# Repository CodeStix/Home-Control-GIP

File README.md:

# Geïntegreerde proef: Home Control

Dit is een repo over mijn eindwerk voor de richting 6 elektriciteit-elektronica. Hier bevinden zich alle scripts, presentaties, schema's, documentaties ...

In het kort: een draadloos home-control systeem waarbij je eenvoudig en snel huishoudelijke apparaten kan aansturen via een gebruiksvriendelijke smartphone app zonder jezelf vragen te stellen over privacy.

Zie documentatie voor uitgebreide informatie.

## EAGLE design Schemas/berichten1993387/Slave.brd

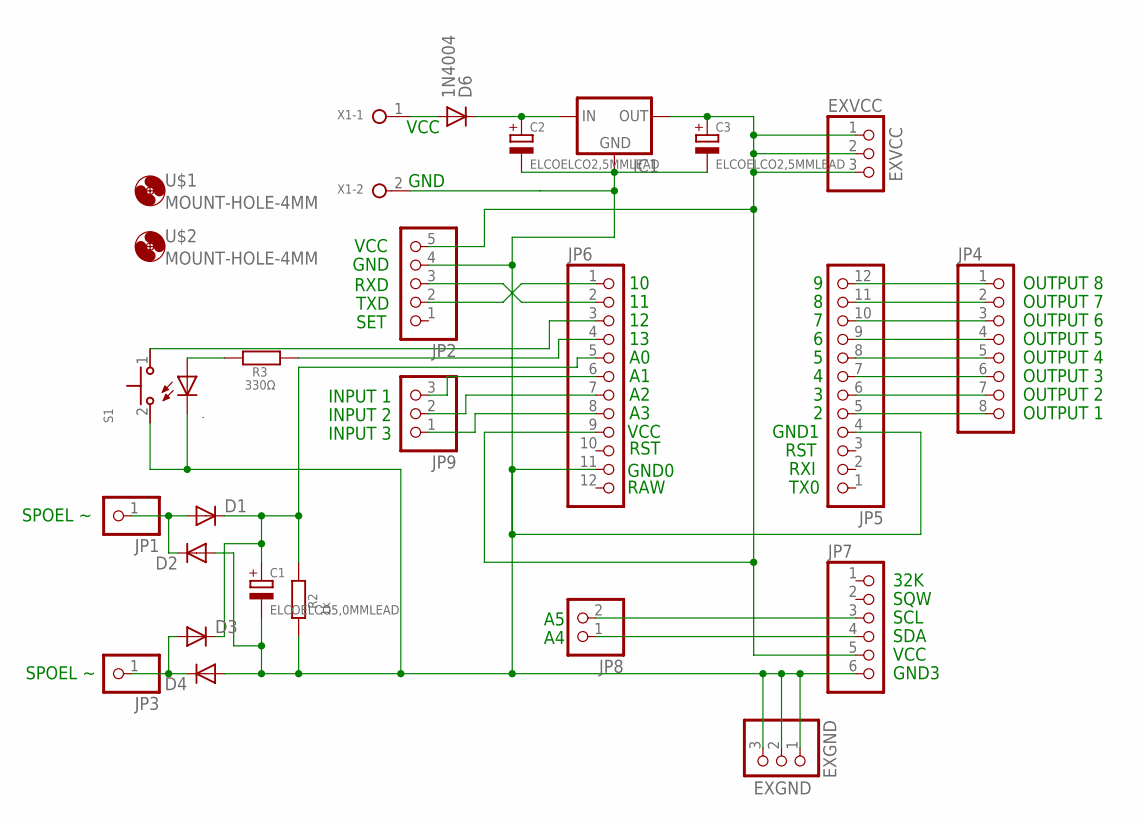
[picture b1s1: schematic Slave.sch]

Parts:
.: LED; CHIPLED_1206
C1: ELCOELCO5,0MMLEAD; ELCO5,0MMLEAD
C2, C3: ELCOELCO2,5MMLEAD; ELCO-2.5MMLEAD
D1, D2, D3, D4, D6: 1N4004; DO41-10
EXGND: PINHD-1X3; 1X03
EXVCC: PINHD-1X3; 1X03
IC1: 78XXS
JP1, JP3: PINHD-1X1; 1X01
JP2: PINHD-1X5; 1X05
JP4: PINHD-1X8; 1X08
JP5, JP6: PINHD-1X12; 1X12
JP7: PINHD-1X6; 1X06
JP8: PINHD-1X2; 1X02
JP9: PINHD-1X3; 1X03
R2: 1k; R1206W
R3: 330Ω; R1206W
S1: MICROSWITCH-B3U-1000P
U$1, U$2: MOUNT-HOLE-4MM; 4,0
X1: TERMINAL-5MM-2POLE; W237-132

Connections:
GND: ..C, C1.-, C2.-, C3.-, D2.A, D4.A, EXGND.1, EXGND.2, EXGND.3, IC1.GND, JP2.4, JP5.4, JP6.11, JP7.6, R2.1, S1.2, X1.2
unnamed: JP7.4, JP8.1
unnamed: JP7.3, JP8.2
unnamed: JP4.1, JP5.12
unnamed: JP4.2, JP5.11
unnamed: JP4.3, JP5.10
unnamed: JP4.4, JP5.9
unnamed: JP4.5, JP5.8
unnamed: JP4.6, JP5.7
unnamed: JP4.7, JP5.6
unnamed: JP4.8, JP5.5
unnamed: D1.A, D2.C, JP1.1
unnamed: C1.+, D1.C, D3.C, JP6.5, R2.2
unnamed: JP6.8, JP9.1
unnamed: D3.A, D4.C, JP3.1
unnamed: JP6.7, JP9.2
unnamed: JP6.6, JP9.3
unnamed: JP2.2, JP6.1
unnamed: JP6.4, R3.2
unnamed: JP2.3, JP6.2
unnamed: ..A, R3.1
unnamed: JP6.3, S1.1
VCC0: D6.A, X1.1
VCC1: C2.+, D6.C, IC1.IN
VCC2: C3.+, EXVCC.1, EXVCC.2, EXVCC.3, IC1.OUT, JP2.5, JP6.9, JP7.5

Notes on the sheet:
RST
RXI
TX0
VCC
RAW
GND0
GND1
OUTPUT 1
OUTPUT 2
OUTPUT 3
OUTPUT 4
OUTPUT 5
OUTPUT 6
OUTPUT 7
OUTPUT 8
GND3
SDA
SCL
SQW
32K
SET
TXD
RXD
GND
INPUT 1
INPUT 2
INPUT 3
SPOEL ~

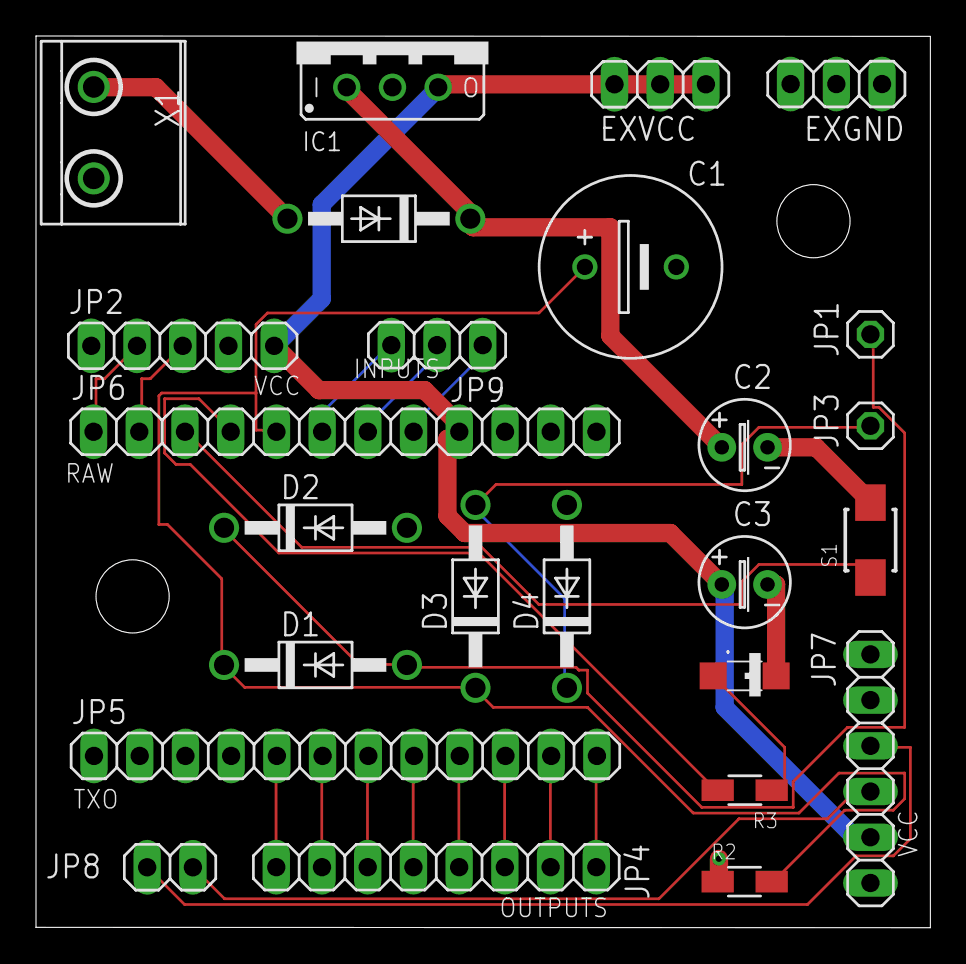
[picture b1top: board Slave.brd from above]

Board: 2 copper layers, 49.7 x 49.5 mm, 27 parts (0 on the bottom side), 25 nets.

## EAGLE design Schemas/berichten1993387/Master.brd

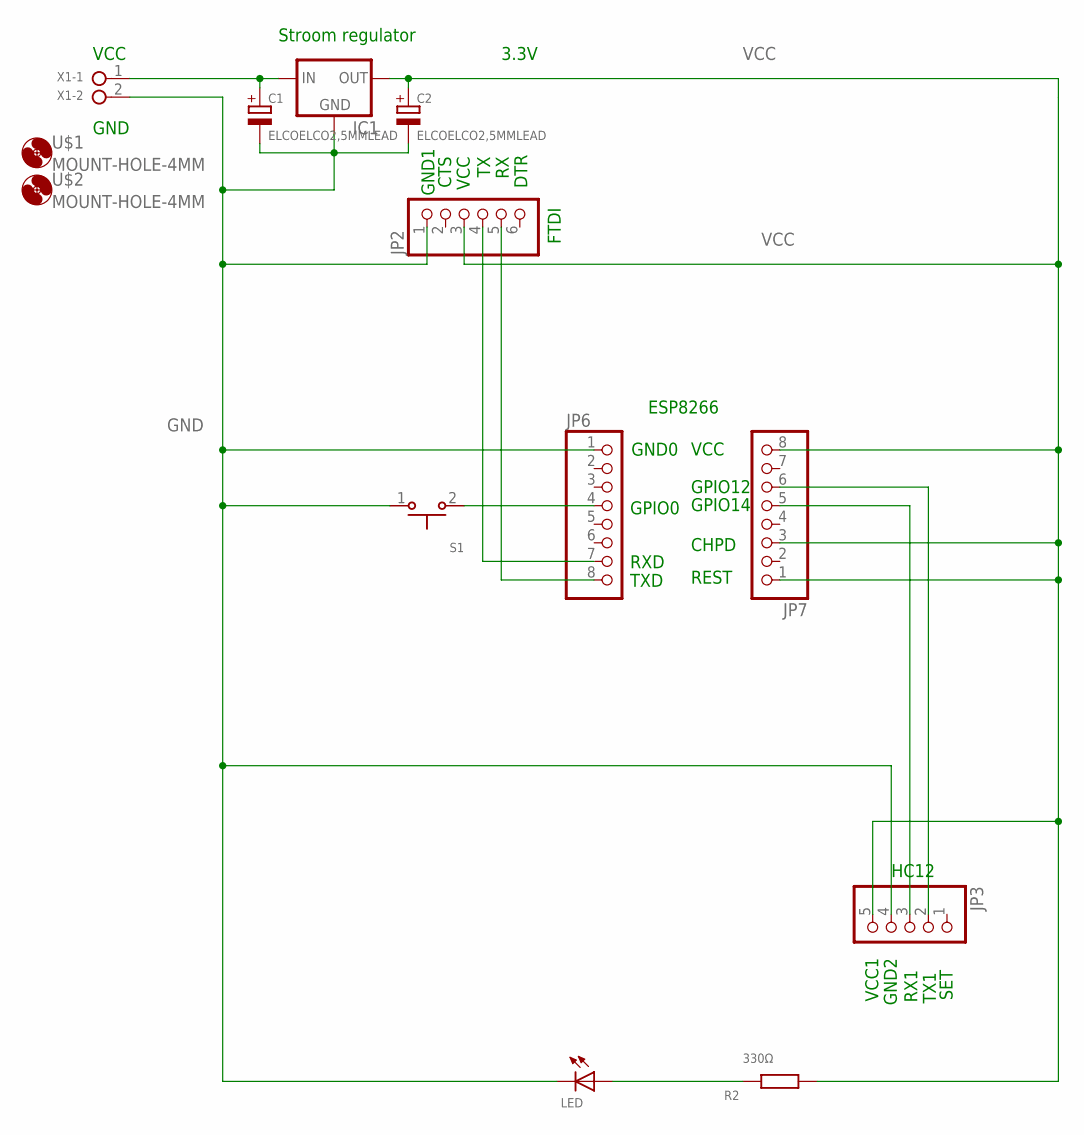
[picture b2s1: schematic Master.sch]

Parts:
C1, C2: ELCOELCO2,5MMLEAD; ELCO-2.5MMLEAD
IC1: LM1117-TO220; TO220V
JP2: PINHD-1X6; 1X06
JP3: PINHD-1X5; 1X05
JP6, JP7: PINHD-1X8; 1X08
LED: LED-SMD1206; CHIPLED_1206
R2: 330Ω; R1206W
S1: MICROSWITCH-B3U-1000P
U$1, U$2: MOUNT-HOLE-4MM; 4,0
X1: TERMINAL-5MM-2POLE; W237-132

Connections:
GND: C1.-, C2.-, IC1.1 (GND), JP2.1, JP3.4, JP6.1, LED.C, S1.1, X1.2
unnamed: LED.A, R2.1
unnamed: JP3.2, JP7.6
unnamed: JP3.3, JP7.5
unnamed: JP6.4, S1.2
unnamed: JP2.5, JP6.8
unnamed: JP2.4, JP6.7
VCC: C2.+, IC1.2 (OUT), JP2.3, JP3.5, JP7.1, JP7.3, JP7.8, R2.2
VIN: C1.+, IC1.3 (IN), X1.1

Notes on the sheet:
3.3V
HC12
FTDI
ESP8266
Stroom regulator
RXD
TXD
GND0
GPIO0
GPIO12
GPIO14
CHPD
REST
VCC
GND
GND2
TX1
RX1
VCC1
SET
DTR
CTS
GND1

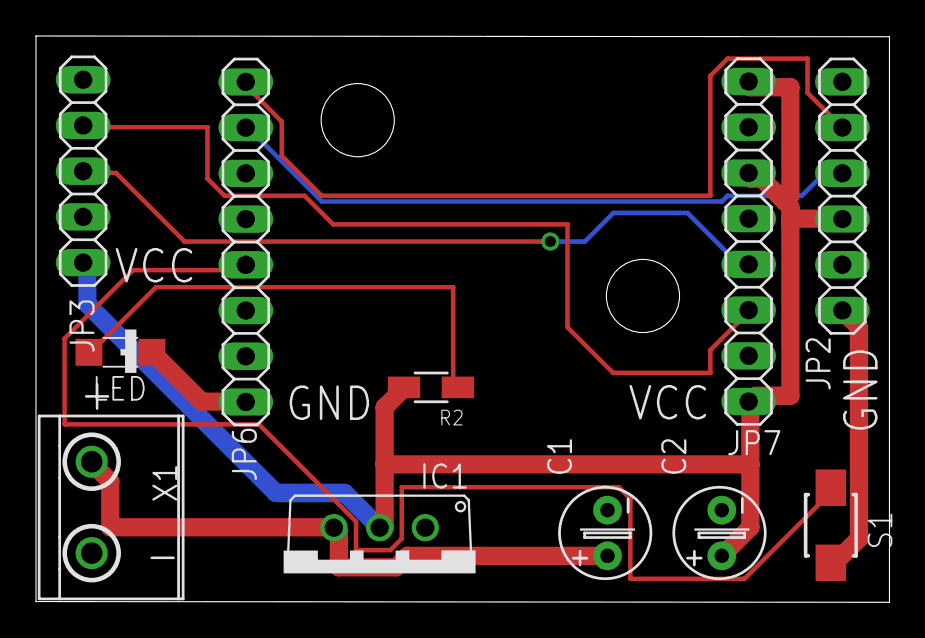
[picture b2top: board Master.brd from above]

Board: 2 copper layers, 47.4 x 31.5 mm, 13 parts (0 on the bottom side), 9 nets.

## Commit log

2018-11-06 led via radio
2018-11-06 besetanden
2018-11-06 bestanden
2018-11-08 qqnpqssom
2019-01-15 vanalles
2019-01-15 renamed folder
2019-01-15 renamed stuff
2019-01-15 verplaatsingen en opruiming
2019-01-15 dir voor schema
2019-01-15 flowcharts toegevoegd
2019-01-16 uploaded HCP
2019-01-20 logboek aangevuld
2019-01-22 resend
2019-01-22 resend v2
2019-01-24 resend v3
2019-01-24 http
2019-01-27 logboek + bijlages
2019-02-12 aanpassingen
2019-02-17 logboeken gemoved
2019-02-19 set fixed
2019-02-22 set command fixed
2019-02-24 logboeken
2019-02-26 checksum communication
2019-03-03 vscode integration
2019-03-12 documentatie upload
2019-03-12 documentatie
2019-03-14 hcp v2
2019-03-15 libraries studio code
2019-03-15 home control v2
2019-03-19 logoek verbetering + hermaak protocol in c
2019-03-21 hcp c++
2019-03-21 c++ hcp
2019-04-02 lots
    Documentation
    App
    Protocol
2019-04-16 Lots of stuff
2019-04-16 Fresh
2019-04-16 Lots of new protocol v4 stuff
2019-04-16 New receiving method
2019-04-16 PacketSenderReceiver
2019-04-18 Request system v1
2019-04-18 Request system v2
2019-04-20 Request system + binding and unbinding
2019-04-20 Device class
2019-04-20 Device saving system v1
2019-04-20 Device saving system v2 + bind/unbind
2019-04-21 Online check system
2019-04-21 Webserver v1
2019-04-21 Logboek week 14 15 16
2019-04-22 Documentatie v1
2019-04-22 Documentatie v2
2019-04-22 Documentatie v3
2019-04-22 Webserver v2
2019-04-22 Webserver v3
2019-04-23 Documentatie + cpp configuration
2019-04-24 Documentatie + Fotos
2019-04-24 Verplaatsen van stuff
2019-04-24 Verplaatsen van stuff 2
2019-04-25 Documentatie afgewerkte versie 1
2019-04-25 Documenatie
2019-05-04 Visual code configurations
2019-05-06 Bind problems fixed
2019-05-06 Created Shared.h and rebind function
2019-05-14 Verbetering dossier
2019-05-17 Icons
2019-05-20 App add and remove and documentation
2019-05-21 Removed build files
2019-05-24 Fix http request problem
2019-05-24 Remove log-booker
2019-05-24 Thinking about property save system
2019-05-26 New data refresh system
2019-05-26 New data refresh system v2
2019-05-26 New data refresh system v3
2019-05-26 Cpp config
2019-05-26 Build
2019-05-27 Documentatie en live data fix
2019-05-27 WebRequest.h
2019-06-03 List changed to JSON support
2019-06-03 Byte to temperature
2019-06-04 Documentatie schema over communicatie tussen master en app
2019-06-04 GRB -> RGB
2019-06-04 App screenshots
2019-06-04 Documentatie definitief
2019-06-20 Lots of fixes
2019-06-20 Chart
2020-01-14 Removed unnecessary python files
2020-08-01 allcode.txt upload
